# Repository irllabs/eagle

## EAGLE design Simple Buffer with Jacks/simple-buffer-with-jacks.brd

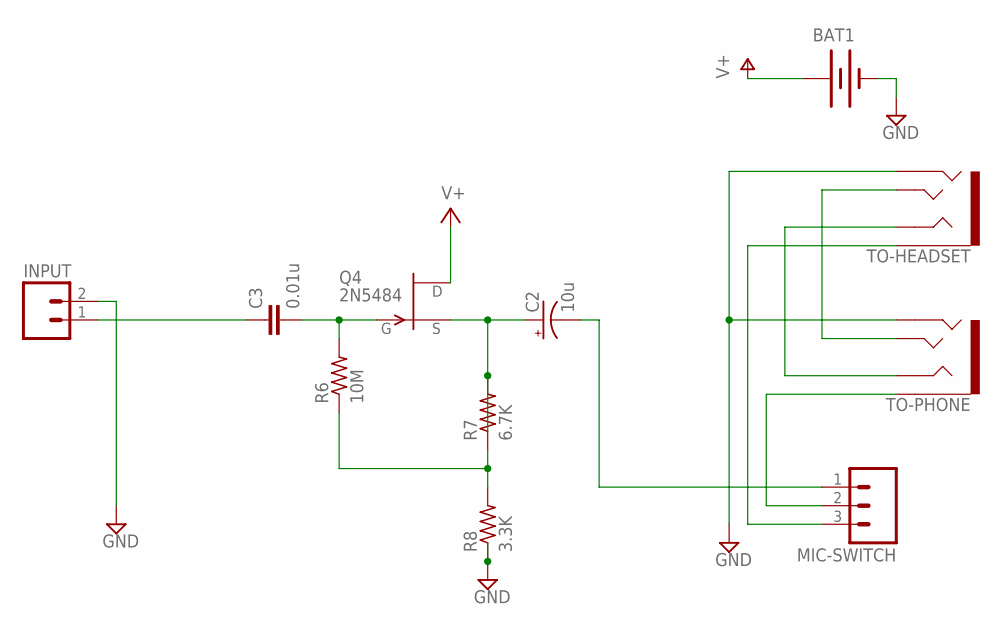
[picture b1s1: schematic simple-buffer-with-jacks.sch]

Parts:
BAT1: BATTERYAAA-KIT; BATTERY-AAA-KIT
C2: 10u; CPOL-RADIAL-10UF-25V
C3: 0.01u; C5B3
INPUT: M02LOCK; 1X02_LOCK
MIC-SWITCH: M03LOCK; 1X03_LOCK
Q4: 2N5484; TO92-
R6: 10M; 0414V
R7: 6.7K; 0414V
R8: 3.3K; 0414V
TO-HEADSET: AUDIO-JACK3; AUDIO-JACK-TRRS-SMD
TO-PHONE: AUDIO-JACK3; AUDIO-JACK-TRRS-SMD

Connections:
GND: BAT1.GND@1 (-), INPUT.2, R8.1, TO-HEADSET.RING2, TO-PHONE.RING2
JFET-GATE: C3.2, Q4.1 (G), R6.2
JFET-SOURCE: C2.1 (+), Q4.2 (S), R7.2
unnamed: C3.1, INPUT.1
unnamed: MIC-SWITCH.3, TO-HEADSET.EARTH
unnamed: TO-HEADSET.TIP, TO-PHONE.TIP
unnamed: TO-HEADSET.RING1, TO-PHONE.RING1
unnamed: R6.1, R7.1, R8.2
TO-PHONE: MIC-SWITCH.2, TO-PHONE.EARTH
V+: BAT1.PWR@1 (+), Q4.3 (D)
`DEL: C2.2 (-)

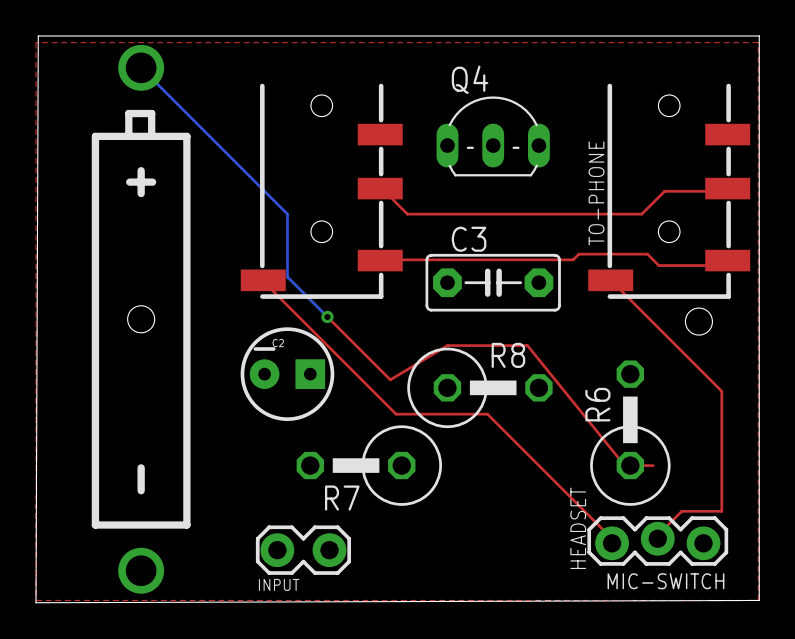
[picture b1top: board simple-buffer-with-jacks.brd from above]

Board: 2 copper layers, 40.2 x 31.5 mm, 11 parts (0 on the bottom side), 10 nets.

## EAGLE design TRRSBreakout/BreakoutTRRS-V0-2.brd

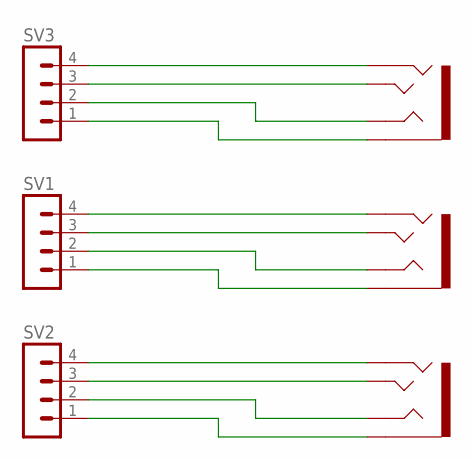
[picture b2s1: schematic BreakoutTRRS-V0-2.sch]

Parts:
SV1, SV2, SV3: MA04-1
TO-HEADSET1, TO-HEADSET2, TO-HEADSET3: AUDIO-JACK3; AUDIO-JACK-TRRS-SMD

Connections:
GND: SV2.4, TO-HEADSET1.RING2
GND1: SV1.4, TO-HEADSET2.RING2
GND2: SV3.4, TO-HEADSET3.RING2
unnamed: SV1.1, TO-HEADSET2.EARTH
unnamed: SV1.3, TO-HEADSET2.TIP
unnamed: SV1.2, TO-HEADSET2.RING1
unnamed: SV3.1, TO-HEADSET3.EARTH
unnamed: SV3.3, TO-HEADSET3.TIP
unnamed: SV3.2, TO-HEADSET3.RING1
unnamed: SV2.1, TO-HEADSET1.EARTH
unnamed: SV2.3, TO-HEADSET1.TIP
unnamed: SV2.2, TO-HEADSET1.RING1

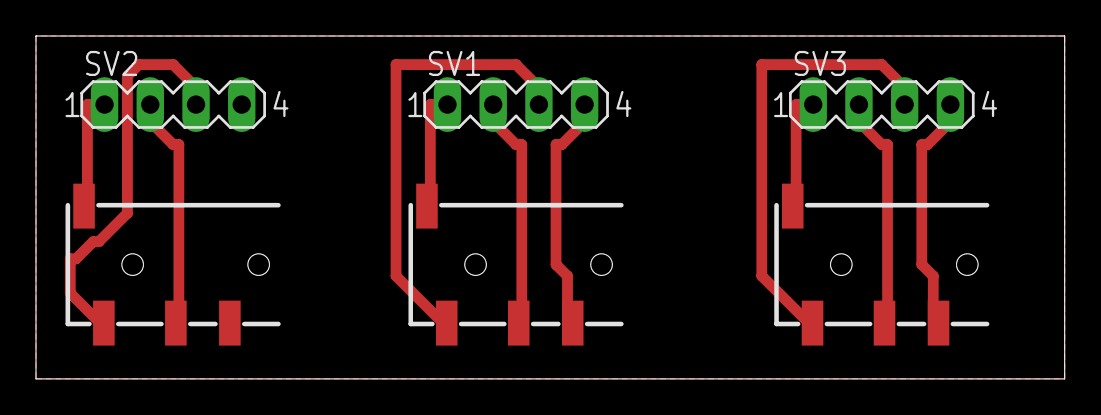
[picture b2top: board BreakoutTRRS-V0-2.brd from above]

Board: 2 copper layers, 57.1 x 19.1 mm, 6 parts (0 on the bottom side), 12 nets.

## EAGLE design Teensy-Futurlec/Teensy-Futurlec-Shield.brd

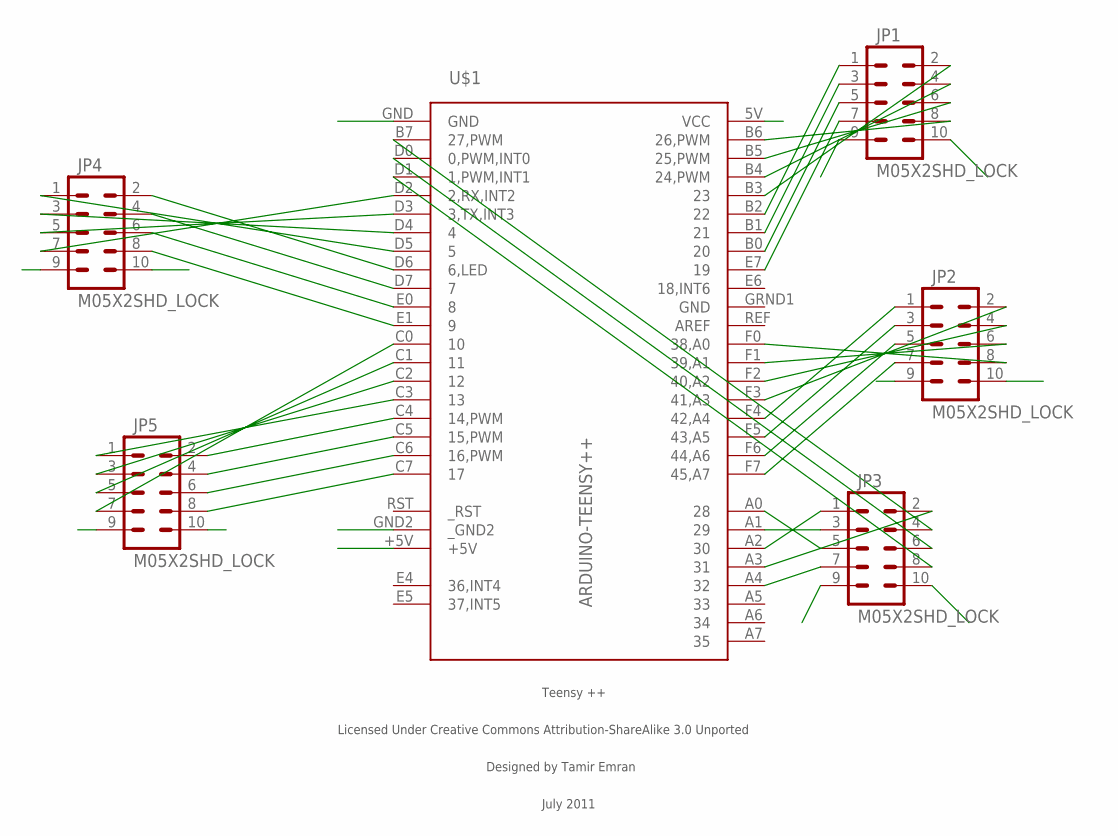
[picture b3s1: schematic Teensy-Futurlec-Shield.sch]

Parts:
JP1, JP2, JP3, JP4, JP5: M05X2SHD_LOCK; 2X5-SHROUDED_LOCK
U$1: ARDUINO-TEENSY++; TEENSY++

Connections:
GND: JP1.10, JP2.10, JP3.10, JP4.10, JP5.10, U$1.GND, U$1.GND2 (_GND2), U$1.GRND1 (GND)
unnamed: JP1.8, U$1.B6 (26,PWM)
unnamed: JP1.6, U$1.B5 (25,PWM)
unnamed: JP1.4, U$1.B4 (24,PWM)
unnamed: JP1.2, U$1.B3 (23)
unnamed: JP1.1, U$1.B2 (22)
unnamed: JP1.3, U$1.B1 (21)
unnamed: JP1.5, U$1.B0 (20)
unnamed: JP1.7, U$1.E7 (19)
unnamed: JP2.6, U$1.F1 (39,A1)
unnamed: JP2.8, U$1.F0 (38,A0)
unnamed: JP2.4, U$1.F2 (40,A2)
unnamed: JP2.2, U$1.F3 (41,A3)
unnamed: JP2.1, U$1.F4 (42,A4)
unnamed: JP2.3, U$1.F5 (43,A5)
unnamed: JP2.5, U$1.F6 (44,A6)
unnamed: JP2.7, U$1.F7 (45,A7)
unnamed: JP5.8, U$1.C7 (17)
unnamed: JP5.6, U$1.C6 (16,PWM)
unnamed: JP5.4, U$1.C5 (15,PWM)
unnamed: JP5.2, U$1.C4 (14,PWM)
unnamed: JP5.1, U$1.C3 (13)
unnamed: JP5.3, U$1.C2 (12)
unnamed: JP5.5, U$1.C1 (11)
unnamed: JP5.7, U$1.C0 (10)
unnamed: JP4.1, U$1.D5 (5)
unnamed: JP4.3, U$1.D4 (4)
unnamed: JP4.5, U$1.D3 (3,TX,INT3)
unnamed: JP4.7, U$1.D2 (2,RX,INT2)
unnamed: JP4.8, U$1.E1 (9)
unnamed: JP4.6, U$1.E0 (8)
unnamed: JP4.4, U$1.D7 (7)
unnamed: JP4.2, U$1.D6 (6,LED)
unnamed: JP3.8, U$1.D1 (1,PWM,INT1)
unnamed: JP3.2, U$1.A3 (31)
unnamed: JP3.6, U$1.D0 (0,PWM,INT0)
unnamed: JP3.4, U$1.B7 (27,PWM)
unnamed: JP3.5, U$1.A0 (28)
unnamed: JP3.3, U$1.A1 (29)
unnamed: JP3.1, U$1.A2 (30)
unnamed: JP3.7, U$1.A4 (32)
VCC: JP1.9, JP2.9, JP3.9, JP4.9, JP5.9, U$1.5V (VCC), U$1.+5V

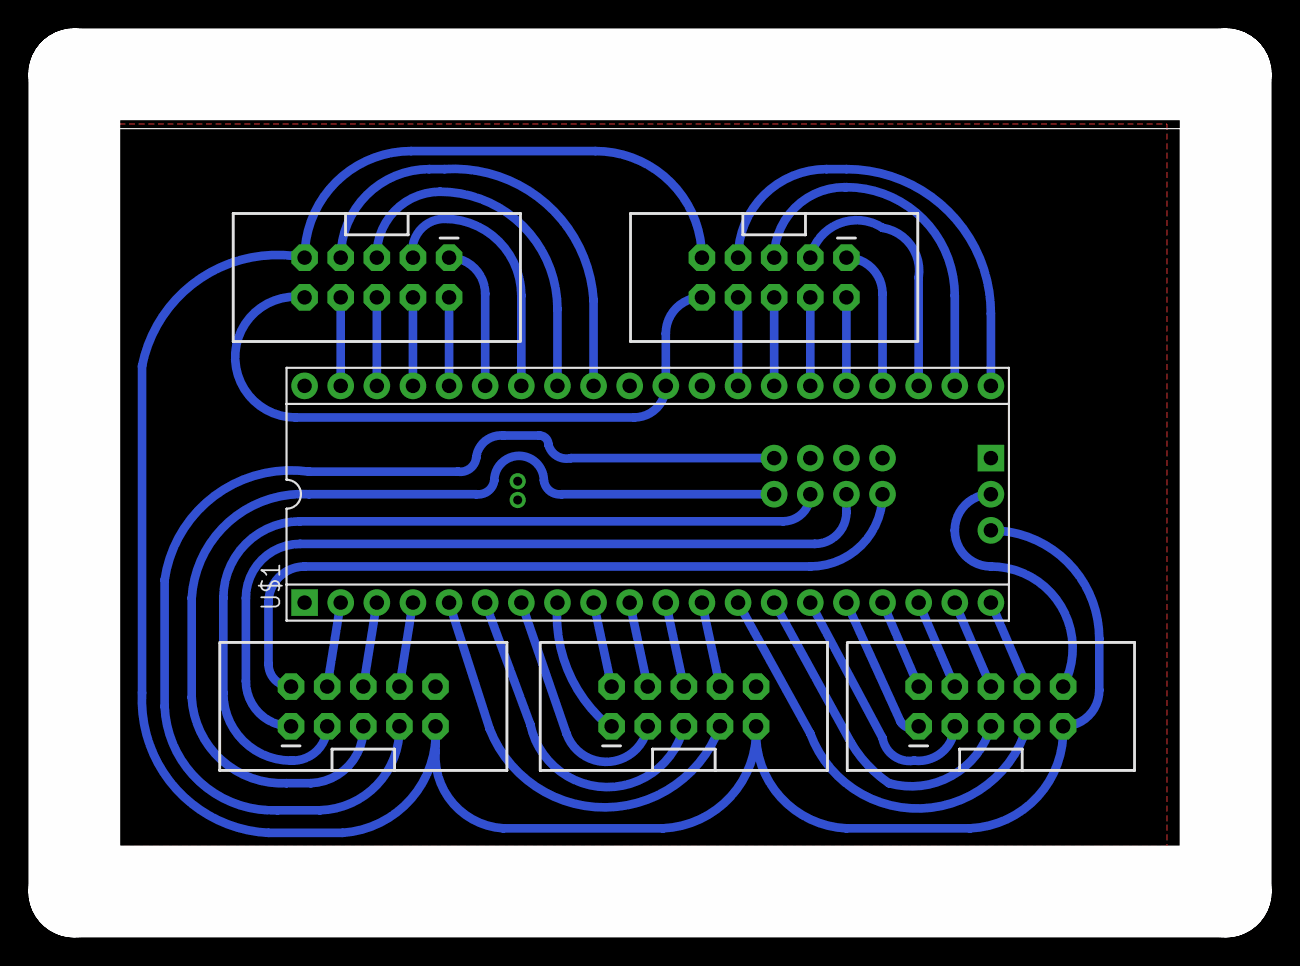
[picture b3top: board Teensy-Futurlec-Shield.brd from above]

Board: 2 copper layers, 81.0 x 57.5 mm, 6 parts (0 on the bottom side), 42 nets.

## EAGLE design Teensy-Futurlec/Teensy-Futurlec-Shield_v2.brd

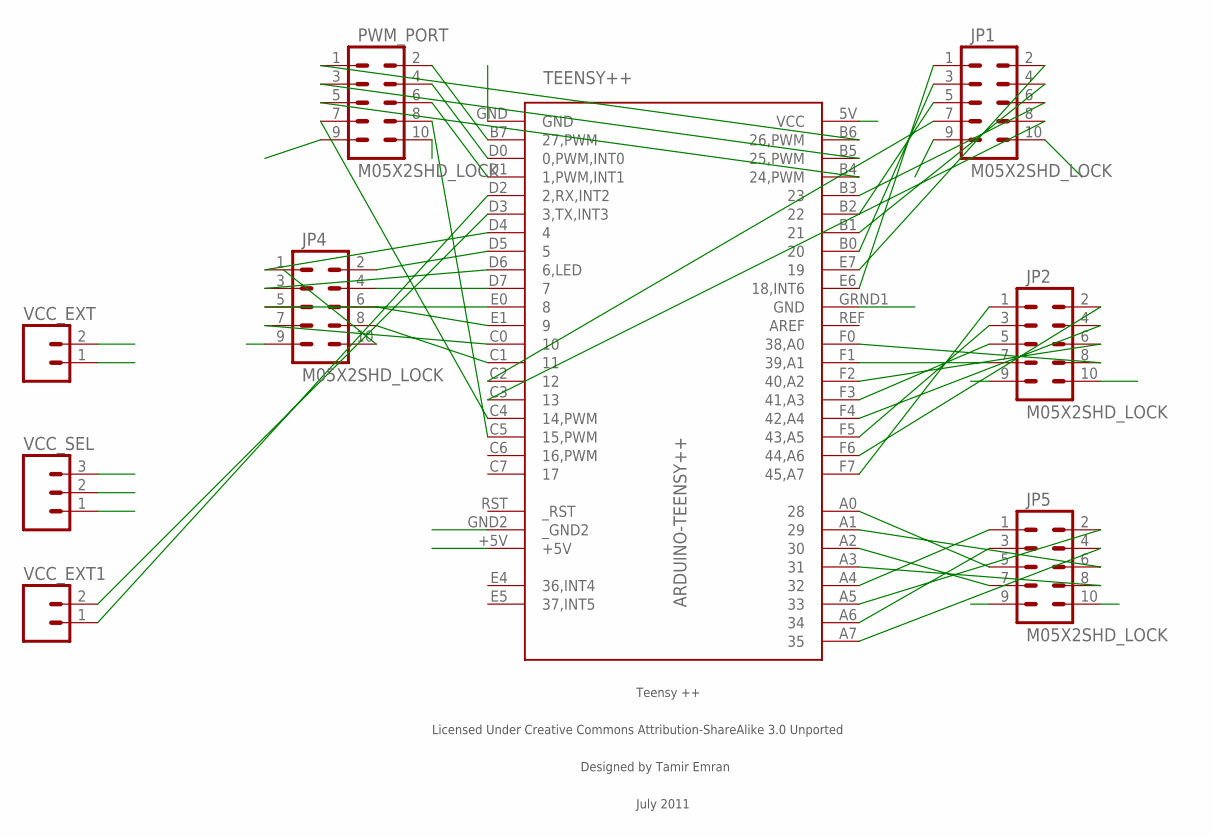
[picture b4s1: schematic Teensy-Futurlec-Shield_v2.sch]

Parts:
JP1, JP2, JP4, JP5: M05X2SHD_LOCK; 2X5-SHROUDED_LOCK
PWM_PORT: M05X2SHD_LOCK; 2X5-SHROUDED_LOCK
TEENSY++: ARDUINO-TEENSY++; TEENSY++
VCC_EXT, VCC_EXT1: M02POLAR_LOCK; MOLEX-1X2_LOCK
VCC_SEL: M03PTH; 1X03

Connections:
GND: JP1.10, JP2.10, JP4.10, JP5.10, PWM_PORT.10, TEENSY++.GND, TEENSY++.GND2 (_GND2), TEENSY++.GRND1 (GND), VCC_EXT.2
unnamed: PWM_PORT.1, TEENSY++.B6 (26,PWM)
unnamed: PWM_PORT.3, TEENSY++.B5 (25,PWM)
unnamed: PWM_PORT.5, TEENSY++.B4 (24,PWM)
unnamed: PWM_PORT.2, TEENSY++.B7 (27,PWM)
unnamed: PWM_PORT.4, TEENSY++.D0 (0,PWM,INT0)
unnamed: PWM_PORT.6, TEENSY++.D1 (1,PWM,INT1)
unnamed: PWM_PORT.8, TEENSY++.C5 (15,PWM)
unnamed: PWM_PORT.7, TEENSY++.C4 (14,PWM)
unnamed: JP2.8, TEENSY++.F0 (38,A0)
unnamed: JP2.7, TEENSY++.F1 (39,A1)
unnamed: JP2.6, TEENSY++.F2 (40,A2)
unnamed: JP2.5, TEENSY++.F3 (41,A3)
unnamed: JP2.4, TEENSY++.F4 (42,A4)
unnamed: JP2.3, TEENSY++.F5 (43,A5)
unnamed: JP2.2, TEENSY++.F6 (44,A6)
unnamed: JP2.1, TEENSY++.F7 (45,A7)
unnamed: JP5.1, TEENSY++.A4 (32)
unnamed: JP1.1, TEENSY++.E6 (18,INT6)
unnamed: JP1.2, TEENSY++.E7 (19)
unnamed: JP1.3, TEENSY++.B0 (20)
unnamed: JP1.4, TEENSY++.B1 (21)
unnamed: JP1.5, TEENSY++.B2 (22)
unnamed: JP1.6, TEENSY++.B3 (23)
unnamed: JP4.5, TEENSY++.E0 (8)
unnamed: JP4.1, TEENSY++.D4 (4)
unnamed: JP4.2, TEENSY++.D5 (5)
unnamed: JP4.6, TEENSY++.E1 (9)
unnamed: JP1.7, TEENSY++.C2 (12)
unnamed: JP4.7, TEENSY++.C0 (10)
unnamed: JP4.8, TEENSY++.C1 (11)
unnamed: JP4.3, TEENSY++.D6 (6,LED)
unnamed: JP4.4, TEENSY++.D7 (7)
unnamed: JP1.8, TEENSY++.C3 (13)
unnamed: JP5.2, TEENSY++.A5 (33)
unnamed: JP5.3, TEENSY++.A6 (34)
unnamed: JP5.4, TEENSY++.A7 (35)
unnamed: JP5.5, TEENSY++.A0 (28)
unnamed: JP5.6, TEENSY++.A1 (29)
unnamed: JP5.7, TEENSY++.A2 (30)
unnamed: JP5.8, TEENSY++.A3 (31)
unnamed: TEENSY++.D2 (2,RX,INT2), VCC_EXT1.1
unnamed: TEENSY++.D3 (3,TX,INT3), VCC_EXT1.2
VCC: JP1.9, JP2.9, JP4.9, JP5.9, PWM_PORT.9, VCC_SEL.2
VCC_EXT: VCC_EXT.1, VCC_SEL.3
VCC_TEENSY: TEENSY++.5V (VCC), TEENSY++.+5V, VCC_SEL.1

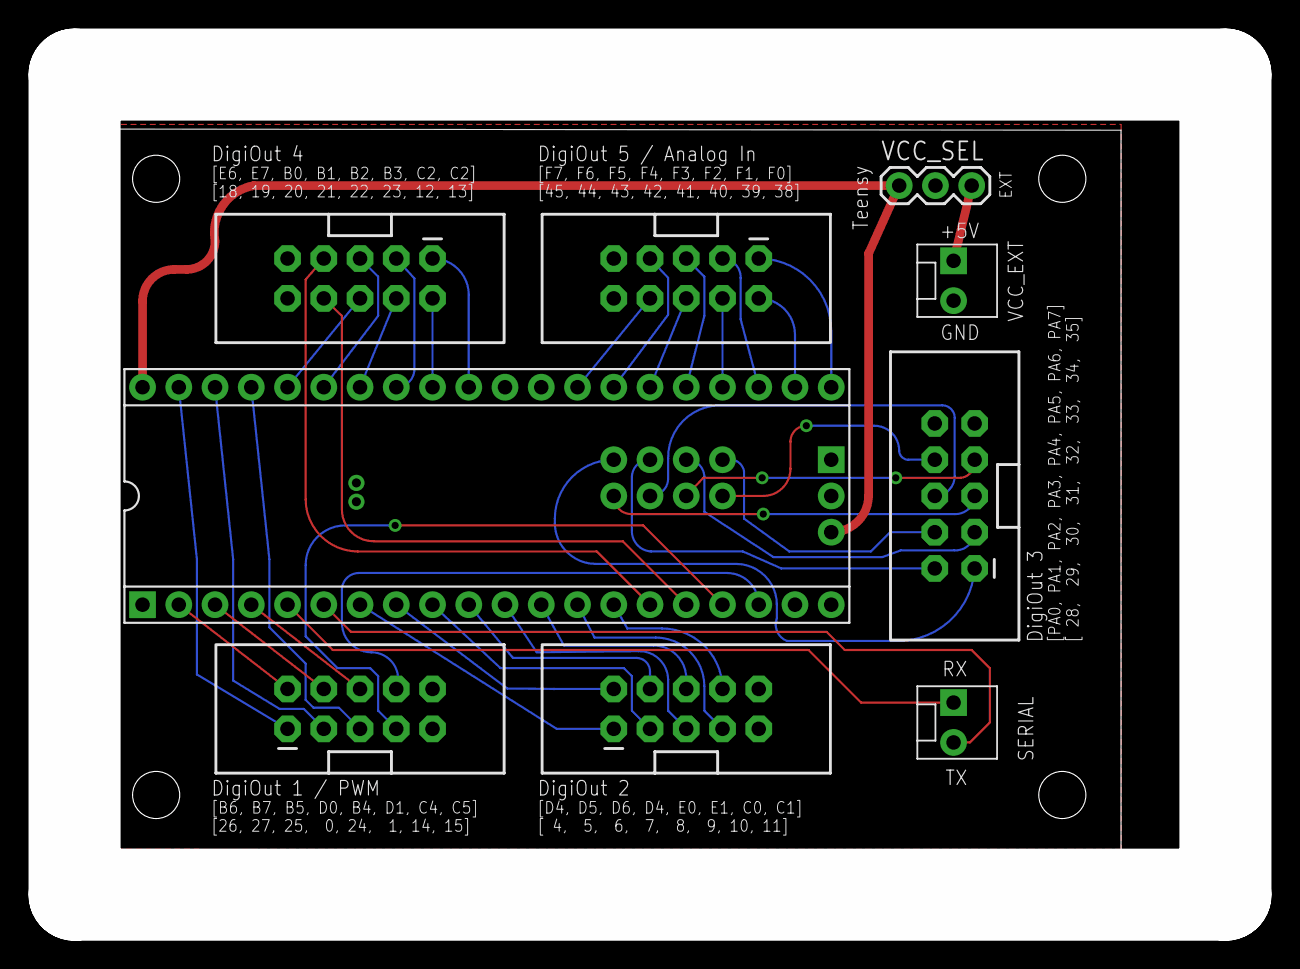
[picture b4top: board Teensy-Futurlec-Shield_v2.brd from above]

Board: 2 copper layers, 80.6 x 57.5 mm, 9 parts (0 on the bottom side), 46 nets.

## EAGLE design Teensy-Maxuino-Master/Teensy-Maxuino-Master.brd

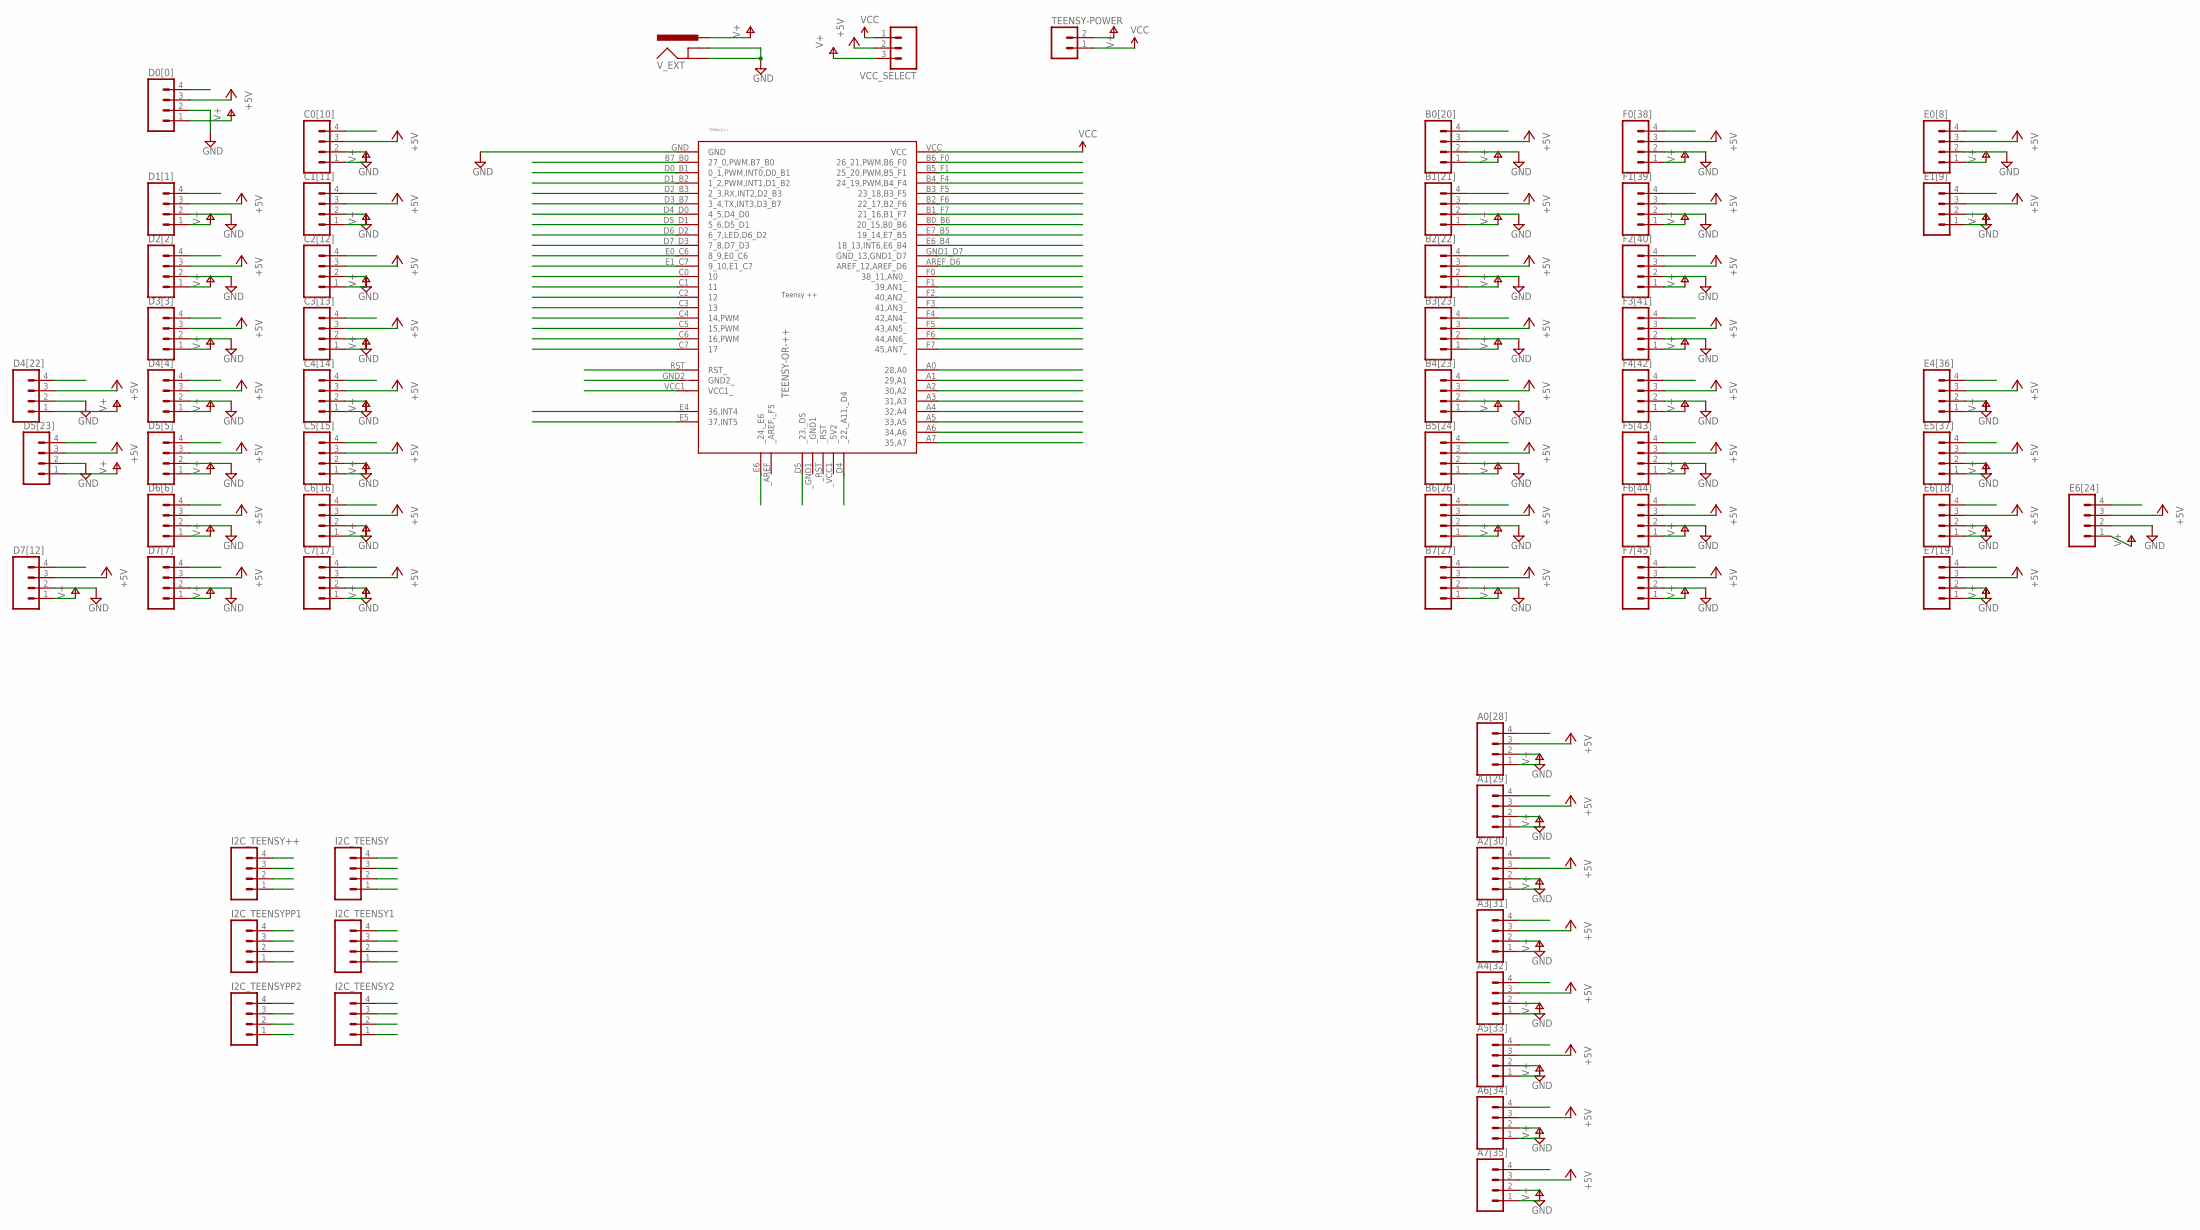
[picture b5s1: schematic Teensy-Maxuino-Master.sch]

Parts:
A0[28], A1[29], A2[30], A3[31], A4[32], A5[33], A6[34], A7[35]: M04PTH; 1X04
B0[20], B1[21], B2[22], B3[23], B4[23], B5[24], B6[26], B7[27]: M04PTH; 1X04
C0[10], C1[11], C2[12], C3[13], C4[14], C5[15], C6[16], C7[17]: M04PTH; 1X04
D0[0], D1[1], D2[2], D3[3], D4[4], D4[22], D5[5], D5[23], D6[6], D7[7], D7[12]: M04PTH; 1X04
E0[8], E1[9], E4[36], E5[37], E6[18], E6[24], E7[19]: M04PTH; 1X04
F0[38], F1[39], F2[40], F3[41], F4[42], F5[43], F6[44], F7[45]: M04PTH; 1X04
I2C_TEENSY, I2C_TEENSY1, I2C_TEENSY2, I2C_TEENSY++, I2C_TEENSYPP1, I2C_TEENSYPP2: M04PTH; 1X04
TEENSY2/++: TEENSY-OR-++
TEENSY-POWER: M02PTH; 1X02
VCC_SELECT: M03PTH; 1X03
V_EXT: POWER_JACKPTH; POWER_JACK_PTH

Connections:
+5V: A0[28].3, A1[29].3, A2[30].3, A3[31].3, A4[32].3, A5[33].3, A6[34].3, A7[35].3, B0[20].3, B1[21].3, B2[22].3, B3[23].3, B4[23].3, B5[24].3, B6[26].3, B7[27].3, C0[10].3, C1[11].3, C2[12].3, C3[13].3, C4[14].3, C5[15].3, C6[16].3, C7[17].3, D0[0].3, D1[1].3, D2[2].3, D3[3].3, D4[4].3, D4[22].3, D5[5].3, D5[23].3, D6[6].3, D7[7].3, D7[12].3, E0[8].3, E1[9].3, E4[36].3, E5[37].3, E6[18].3, E6[24].3, E7[19].3, F0[38].3, F1[39].3, F2[40].3, F3[41].3, F4[42].3, F5[43].3, F6[44].3, F7[45].3, VCC_SELECT.2
A0: A0[28].4, TEENSY2/++.A0 (28,A0)
A1: A1[29].4, TEENSY2/++.A1 (29,A1)
A2: A2[30].4, TEENSY2/++.A2 (30,A2)
A3: A3[31].4, TEENSY2/++.A3 (31,A3)
A4: A4[32].4, TEENSY2/++.A4 (32,A4)
A5: A5[33].4, TEENSY2/++.A5 (33,A5)
A6: A6[34].4, TEENSY2/++.A6 (34,A6)
A7: A7[35].4, TEENSY2/++.A7 (35,A7)
AREF_D6: TEENSY2/++.AREF_D6 (AREF_12,AREF_D6)
B0_B6: B0[20].4, TEENSY2/++.B0_B6 (20_15,B0_B6)
B1_F7: B1[21].4, TEENSY2/++.B1_F7 (21_16,B1_F7)
B2_F6: B2[22].4, TEENSY2/++.B2_F6 (22_17,B2_F6)
B3_F5: B3[23].4, TEENSY2/++.B3_F5 (23_18,B3_F5)
B4_F4: B4[23].4, TEENSY2/++.B4_F4 (24_19,PWM,B4_F4)
B5_F1: B5[24].4, TEENSY2/++.B5_F1 (25_20,PWM,B5_F1)
B6_F0: B6[26].4, TEENSY2/++.B6_F0 (26_21,PWM,B6_F0)
B7_B0: B7[27].4, TEENSY2/++.B7_B0 (27_0,PWM,B7_B0)
C0: C0[10].4, TEENSY2/++.C0 (10)
C1: C1[11].4, TEENSY2/++.C1 (11)
C2: C2[12].4, TEENSY2/++.C2 (12)
C3: C3[13].4, TEENSY2/++.C3 (13)
C4: C4[14].4, TEENSY2/++.C4 (14,PWM)
C5: C5[15].4, TEENSY2/++.C5 (15,PWM)
C6: C6[16].4, TEENSY2/++.C6 (16,PWM)
C7: C7[17].4, TEENSY2/++.C7 (17)
D0_B1: D0[0].4, I2C_TEENSY++.4, I2C_TEENSYPP1.4, I2C_TEENSYPP2.4, TEENSY2/++.D0_B1 (0_1,PWM,INT0,D0_B1)
D1_B2: D1[1].4, I2C_TEENSY++.3, I2C_TEENSYPP1.3, I2C_TEENSYPP2.3, TEENSY2/++.D1_B2 (1_2,PWM,INT1,D1_B2)
D2_B3: D2[2].4, TEENSY2/++.D2_B3 (2_3,RX,INT2,D2_B3)
D3_B7: D3[3].4, TEENSY2/++.D3_B7 (3_4,TX,INT3,D3_B7)
D4_D0: D4[4].4, I2C_TEENSY.4, I2C_TEENSY1.4, I2C_TEENSY2.4, TEENSY2/++.D4_D0 (4_5,D4_D0)
D5_D1: D5[5].4, I2C_TEENSY.3, I2C_TEENSY1.3, I2C_TEENSY2.3, TEENSY2/++.D5_D1 (5_6,D5_D1)
D6_D2: D6[6].4, TEENSY2/++.D6_D2 (6_7,LED,D6_D2)
D7_D3: D7[7].4, TEENSY2/++.D7_D3 (7_8,D7_D3)
E0_C6: E0[8].4, TEENSY2/++.E0_C6 (8_9,E0_C6)
E1_C7: E1[9].4, TEENSY2/++.E1_C7 (9_10,E1_C7)
E4: E4[36].4, TEENSY2/++.E4 (36,INT4)
E5: E5[37].4, TEENSY2/++.E5 (37,INT5)
E6_B4: E6[18].4, TEENSY2/++.E6_B4 (18_13,INT6,E6_B4)
E7_B5: E7[19].4, TEENSY2/++.E7_B5 (19_14,E7_B5)
F0: F0[38].4, TEENSY2/++.F0 (38_11,AN0_)
F1: F1[39].4, TEENSY2/++.F1 (39,AN1_)
F2: F2[40].4, TEENSY2/++.F2 (40,AN2_)
F3: F3[41].4, TEENSY2/++.F3 (41,AN3_)
F4: F4[42].4, TEENSY2/++.F4 (42,AN4_)
F5: F5[43].4, TEENSY2/++.F5 (43,AN5_)
F6: F6[44].4, TEENSY2/++.F6 (44,AN6_)
F7: F7[45].4, TEENSY2/++.F7 (45,AN7_)
GND: A0[28].2, A1[29].2, A2[30].2, A3[31].2, A4[32].2, A5[33].2, A6[34].2, A7[35].2, B0[20].2, B1[21].2, B2[22].2, B3[23].2, B4[23].2, B5[24].2, B6[26].2, B7[27].2, C0[10].2, C1[11].2, C2[12].2, C3[13].2, C4[14].2, C5[15].2, C6[16].2, C7[17].2, D0[0].2, D1[1].2, D2[2].2, D3[3].2, D4[4].2, D4[22].2, D5[5].2, D5[23].2, D6[6].2, D7[7].2, D7[12].2, E0[8].2, E1[9].2, E4[36].2, E5[37].2, E6[18].2, E6[24].2, E7[19].2, F0[38].2, F1[39].2, F2[40].2, F3[41].2, F4[42].2, F5[43].2, F6[44].2, F7[45].2, I2C_TEENSY.1, I2C_TEENSY1.1, I2C_TEENSY2.1, I2C_TEENSY++.1, I2C_TEENSYPP1.1, I2C_TEENSYPP2.1, TEENSY2/++.GND, V_EXT.GND, V_EXT.GNDBREAK
GND1_D7: D7[12].4, TEENSY2/++.GND1_D7 (GND_13,GND1_D7)
GND2: TEENSY2/++.GND2_
NFO: A0[28].1, A1[29].1, A2[30].1, A3[31].1, A4[32].1, A5[33].1, A6[34].1, A7[35].1, B0[20].1, B1[21].1, B2[22].1, B3[23].1, B4[23].1, B5[24].1, B6[26].1, B7[27].1, C0[10].1, C1[11].1, C2[12].1, C3[13].1, C4[14].1, C5[15].1, C6[16].1, C7[17].1, D0[0].1, D1[1].1, D2[2].1, D3[3].1, D4[4].1, D4[22].1, D5[5].1, D5[23].1, D6[6].1, D7[7].1, D7[12].1, E0[8].1, E1[9].1, E4[36].1, E5[37].1, E6[18].1, E6[24].1, E7[19].1, F0[38].1, F1[39].1, F2[40].1, F3[41].1, F4[42].1, F5[43].1, F6[44].1, F7[45].1, TEENSY-POWER.2, VCC_SELECT.3, V_EXT.PWR
RST: TEENSY2/++.RST_
VCC: I2C_TEENSY.2, I2C_TEENSY1.2, I2C_TEENSY2.2, I2C_TEENSY++.2, I2C_TEENSYPP1.2, I2C_TEENSYPP2.2, TEENSY2/++.VCC, TEENSY-POWER.1, VCC_SELECT.1
VCC1: TEENSY2/++.VCC1_
_D4: D4[22].4, TEENSY2/++._D4 (_22,_A11,_D4)
_D5: D5[23].4, TEENSY2/++._D5 (_23,_D5)
_E6: E6[24].4, TEENSY2/++._E6 (_24,_E6)

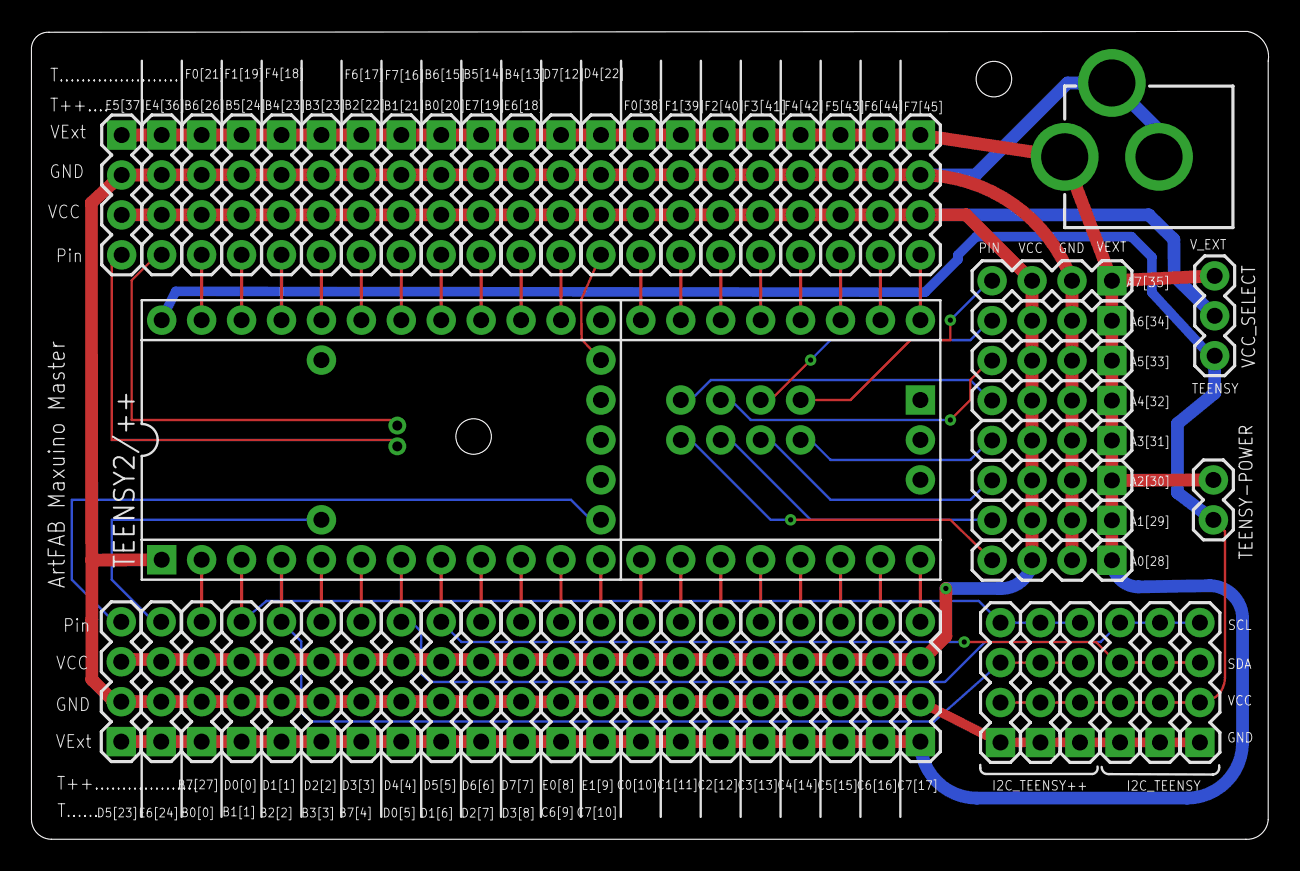
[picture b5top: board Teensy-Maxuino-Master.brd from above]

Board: 2 copper layers, 78.7 x 51.4 mm, 60 parts (0 on the bottom side), 54 nets.

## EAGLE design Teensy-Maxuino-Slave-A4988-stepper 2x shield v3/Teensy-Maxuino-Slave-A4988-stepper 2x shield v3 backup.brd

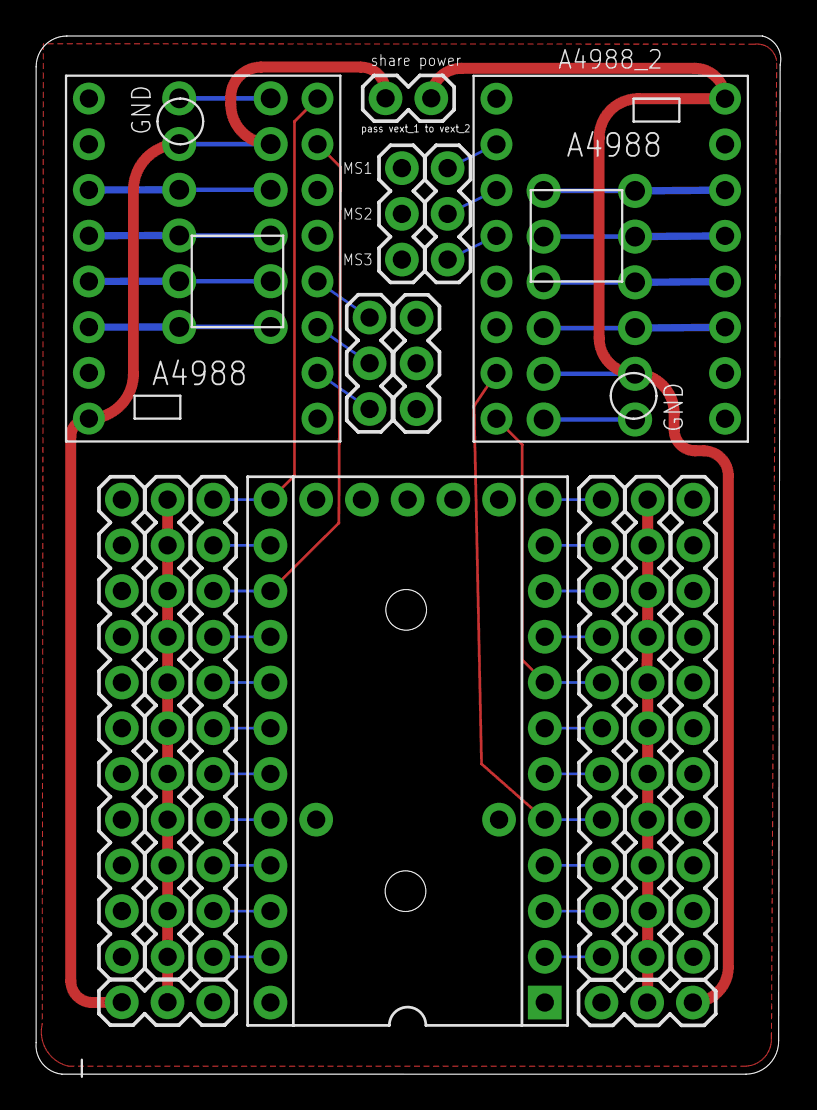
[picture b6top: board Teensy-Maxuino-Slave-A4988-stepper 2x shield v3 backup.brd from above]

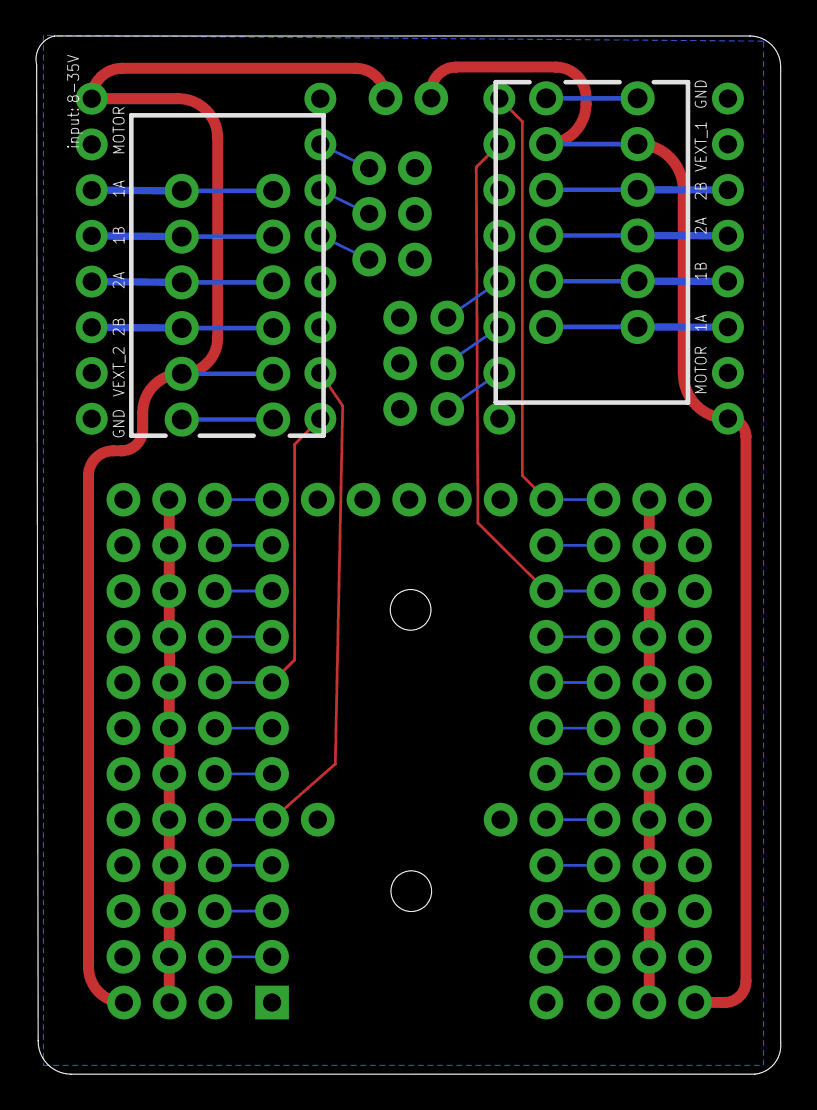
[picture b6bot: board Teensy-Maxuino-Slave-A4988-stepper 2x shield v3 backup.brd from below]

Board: 2 copper layers, 41.4 x 57.7 mm, 18 parts (2 on the bottom side), 44 nets.

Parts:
+5V, +5V1: 1X03
A4988_1, A4988_2: POLOLU_A4988
GND_1, GND_2: M11PTH; 1X11
MICROSTEP, MICROSTEP1: 1X03
PINS_1, PINS_2: M11PTH; 1X11
SHARE: 1X02
STEPPER, STEPPER1: SPRINGTERMINAL-2.54MM-6
V+_1, V+_2: M11PTH; 1X11
VSEL_1, VSEL_2: 1X03
_1: TEENSY

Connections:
+5V: +5V.1, +5V.2, +5V.3, +5V1.1, +5V1.2, +5V1.3, A4988_1.VDD, A4988_2.VDD, VSEL_1.3, VSEL_2.3, _1.+5V
DIR: A4988_1.DIR, PINS_2.11, _1.D6
DIR1: A4988_2.DIR, PINS_1.5, _1.D1
GND: A4988_1.GND, A4988_1.GND_MOT, A4988_2.GND, A4988_2.GND_MOT, GND_1.1, GND_1.2, GND_1.3, GND_1.4, GND_1.5, GND_1.6, GND_1.7, GND_1.8, GND_1.9, GND_1.10, GND_1.11, GND_2.1, GND_2.2, GND_2.3, GND_2.4, GND_2.5, GND_2.6, GND_2.7, GND_2.8, GND_2.9, GND_2.10, GND_2.11, STEPPER.P$6, STEPPER1.P$6, _1.GND
unnamed: A4988_1.2B, STEPPER.P$4
unnamed: A4988_1.2A, STEPPER.P$3
unnamed: A4988_1.1A, STEPPER.P$2
unnamed: A4988_1.1B, STEPPER.P$1
unnamed: A4988_2.RST, A4988_2.SLP
unnamed: A4988_1.RST, A4988_1.SLP
unnamed: A4988_2.MS1, MICROSTEP1.3
unnamed: A4988_1.MS1, MICROSTEP.3
unnamed: A4988_1.MS2, MICROSTEP.2
unnamed: A4988_1.MS3, MICROSTEP.1
unnamed: A4988_2.MS2, MICROSTEP1.2
unnamed: A4988_2.MS3, MICROSTEP1.1
unnamed: A4988_2.2B, STEPPER1.P$4
unnamed: A4988_2.2A, STEPPER1.P$3
unnamed: A4988_2.1A, STEPPER1.P$2
unnamed: A4988_2.1B, STEPPER1.P$1
unnamed: PINS_1.11, _1.B0
unnamed: PINS_1.6, _1.D0
unnamed: PINS_1.7, _1.B7
unnamed: PINS_1.2, _1.C6
unnamed: PINS_1.3, _1.D3
unnamed: PINS_1.4, _1.D2
unnamed: PINS_1.1, _1.C7
unnamed: PINS_1.9, _1.B2
unnamed: PINS_1.10, _1.B1
unnamed: PINS_2.3, _1.F4
unnamed: PINS_2.4, _1.F5
unnamed: PINS_2.5, _1.F6
unnamed: PINS_2.6, _1.F7
unnamed: PINS_2.7, _1.B6
unnamed: PINS_2.8, _1.B5
unnamed: PINS_2.10, _1.D7
unnamed: PINS_2.1, _1.F0
unnamed: PINS_2.2, _1.F1
STEP: A4988_1.STEP, PINS_2.9, _1.B4
STEP1: A4988_2.STEP, PINS_1.8, _1.B3
V+_1: V+_1.1, V+_1.2, V+_1.3, V+_1.4, V+_1.5, V+_1.6, V+_1.7, V+_1.8, V+_1.9, V+_1.10, V+_1.11, VSEL_1.2
V+_2: V+_2.1, V+_2.2, V+_2.3, V+_2.4, V+_2.5, V+_2.6, V+_2.7, V+_2.8, V+_2.9, V+_2.10, V+_2.11, VSEL_2.2
VIN: A4988_1.V_MOT, SHARE.1, STEPPER.P$5, VSEL_2.1
VIN_2: A4988_2.V_MOT, SHARE.2, STEPPER1.P$5, VSEL_1.1

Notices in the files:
parts and their libraries:
SparkFun-Connectors: Licensing: Creative Commons ShareAlike 4.0 International - https://creativecommons.org/licenses/by-sa/4.0
SparkFun-Passives: Licensing: CC v3.0 Share-Alike You are welcome to use this library for commercial purposes.
teensypp: Licensed Under Creative Commons
